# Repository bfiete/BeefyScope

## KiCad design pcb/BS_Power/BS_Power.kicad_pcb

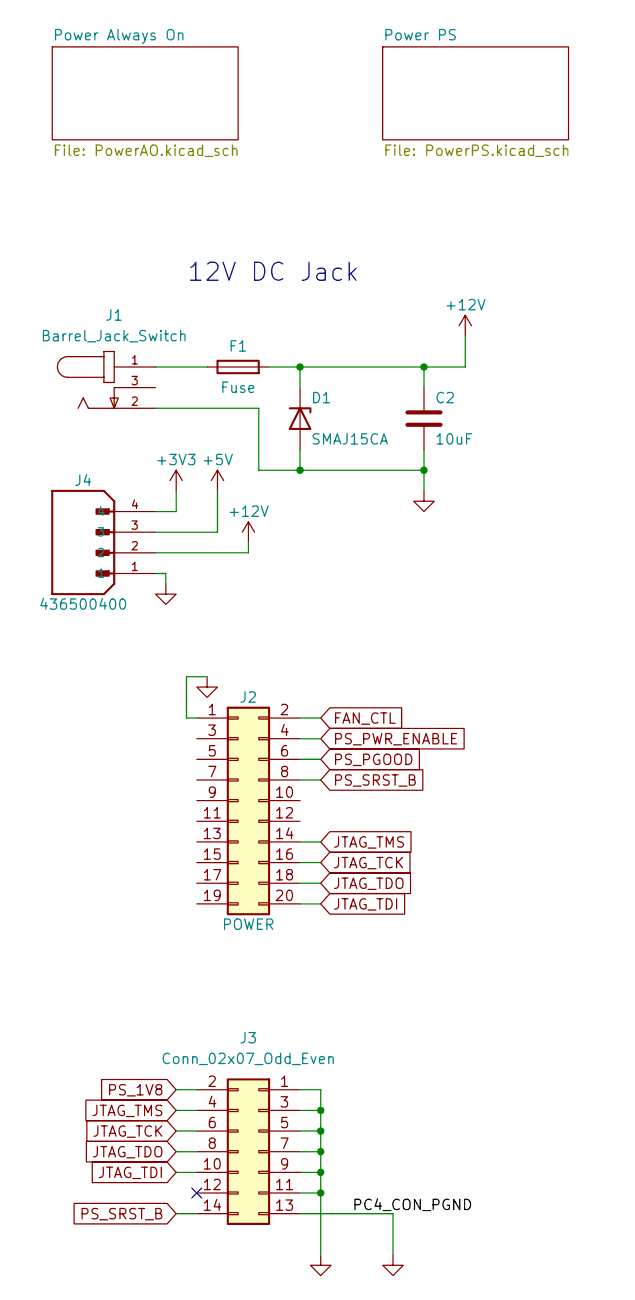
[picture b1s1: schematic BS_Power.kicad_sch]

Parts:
C2: 10uF; C_0805_2012Metric
D1: SMAJ15CA; D_SMA; LCSC Part C353477
F1: Fuse; FUSE_C206912; LCSC Part C206912
J1: Barrel_Jack_Switch; CUI_PJ-202BH; PART_REV 1.02; JLCPCB BOM 0
J2: POWER; IDC-Header_2x10_P2.54mm_Vertical; LCSC Part C9144
J3: Conn_02x07_Odd_Even; PinHeader_2x07_P2.00mm_Vertical; LCSC Part C146614
J4: 436500400; MOLEX_436500400; PARTREV D7; LCSC Part C277684

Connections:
+3V3: J4.4; also elsewhere on the board
+5V: J4.3; also elsewhere on the board
+12V: C2.1, D1.1 (K), F1.2, J4.2; also elsewhere on the board
FAN_CTL: J2.2
GND: C2.2, D1.2 (A), J1.2, J2.1, J3.1, J3.3, J3.5, J3.7, J3.9, J3.11, J3.13, J4.1; also elsewhere on the board
JTAG_TCK: J2.16, J3.6
JTAG_TDI: J2.20, J3.10
JTAG_TDO: J2.18, J3.8
JTAG_TMS: J2.14, J3.4
unnamed: F1.1, J1.1
PS_1V8: J3.2
PS_PGOOD: J2.6; also elsewhere on the board
PS_PWR_ENABLE: J2.4; also elsewhere on the board
PS_SRST_B: J2.8, J3.14

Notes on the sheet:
12V DC Jack

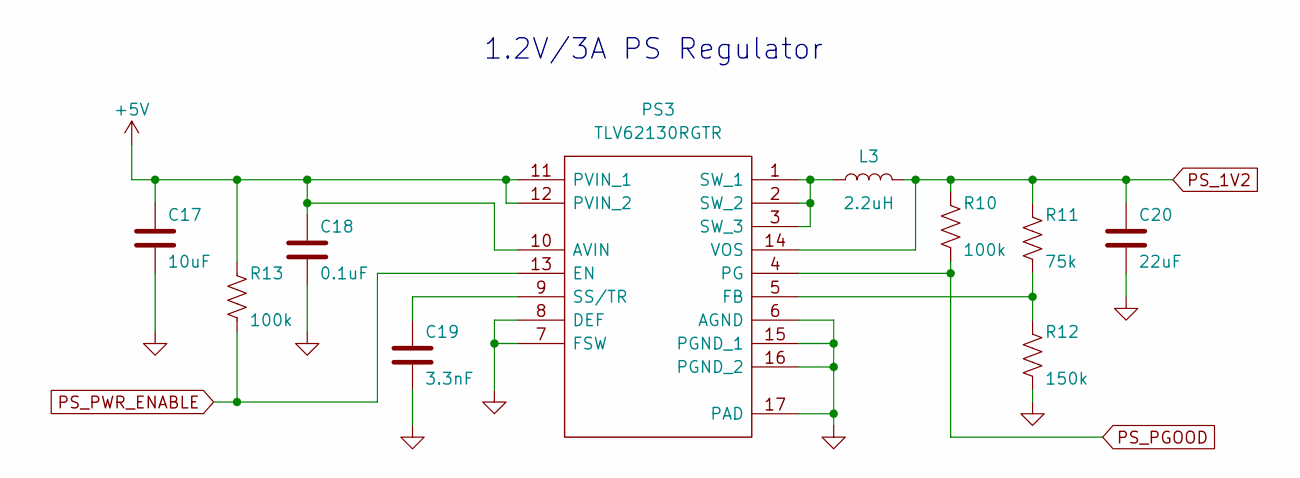
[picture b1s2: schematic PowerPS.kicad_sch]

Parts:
C17: 10uF; C_0805_2012Metric
C18: 0.1uF; C_0603_1608Metric
C19: 3.3nF; C_0603_1608Metric
C20: 22uF; C_0805_2012Metric
L3: 2.2uH; L_4.1x4.5; LCSC Part C2847469
PS3: TLV62130RGTR; QFN50P300X300X100-17N-D; Mouser Part Number 595-TLV62130RGTR
R10, R13: 100k; R_0603_1608Metric
R11: 75k; R_0603_1608Metric; LCSC Part C23240
R12: 150k; R_0603_1608Metric; LCSC Part C22807

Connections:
+5V: C17.1, C18.1, PS3.10 (AVIN), PS3.11 (PVIN_1), PS3.12 (PVIN_2), R13.1; also elsewhere on the board
GND: C17.2, C18.2, C19.1, C20.2, PS3.6 (AGND), PS3.7 (FSW), PS3.8 (DEF), PS3.15 (PGND_1), PS3.16 (PGND_2), PS3.17 (PAD), R12.2; also elsewhere on the board
unnamed: C19.2, PS3.9 (SS/TR)
unnamed: L3.1, PS3.1 (SW_1), PS3.2 (SW_2), PS3.3 (SW_3)
unnamed: PS3.5 (FB), R11.2, R12.1
PS_1V2: C20.1, L3.2, PS3.14 (VOS), R10.1, R11.1
PS_PGOOD: PS3.4 (PG), R10.2; also elsewhere on the board
PS_PWR_ENABLE: PS3.13 (EN), R13.2; also elsewhere on the board

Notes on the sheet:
1.2V/3A PS Regulator

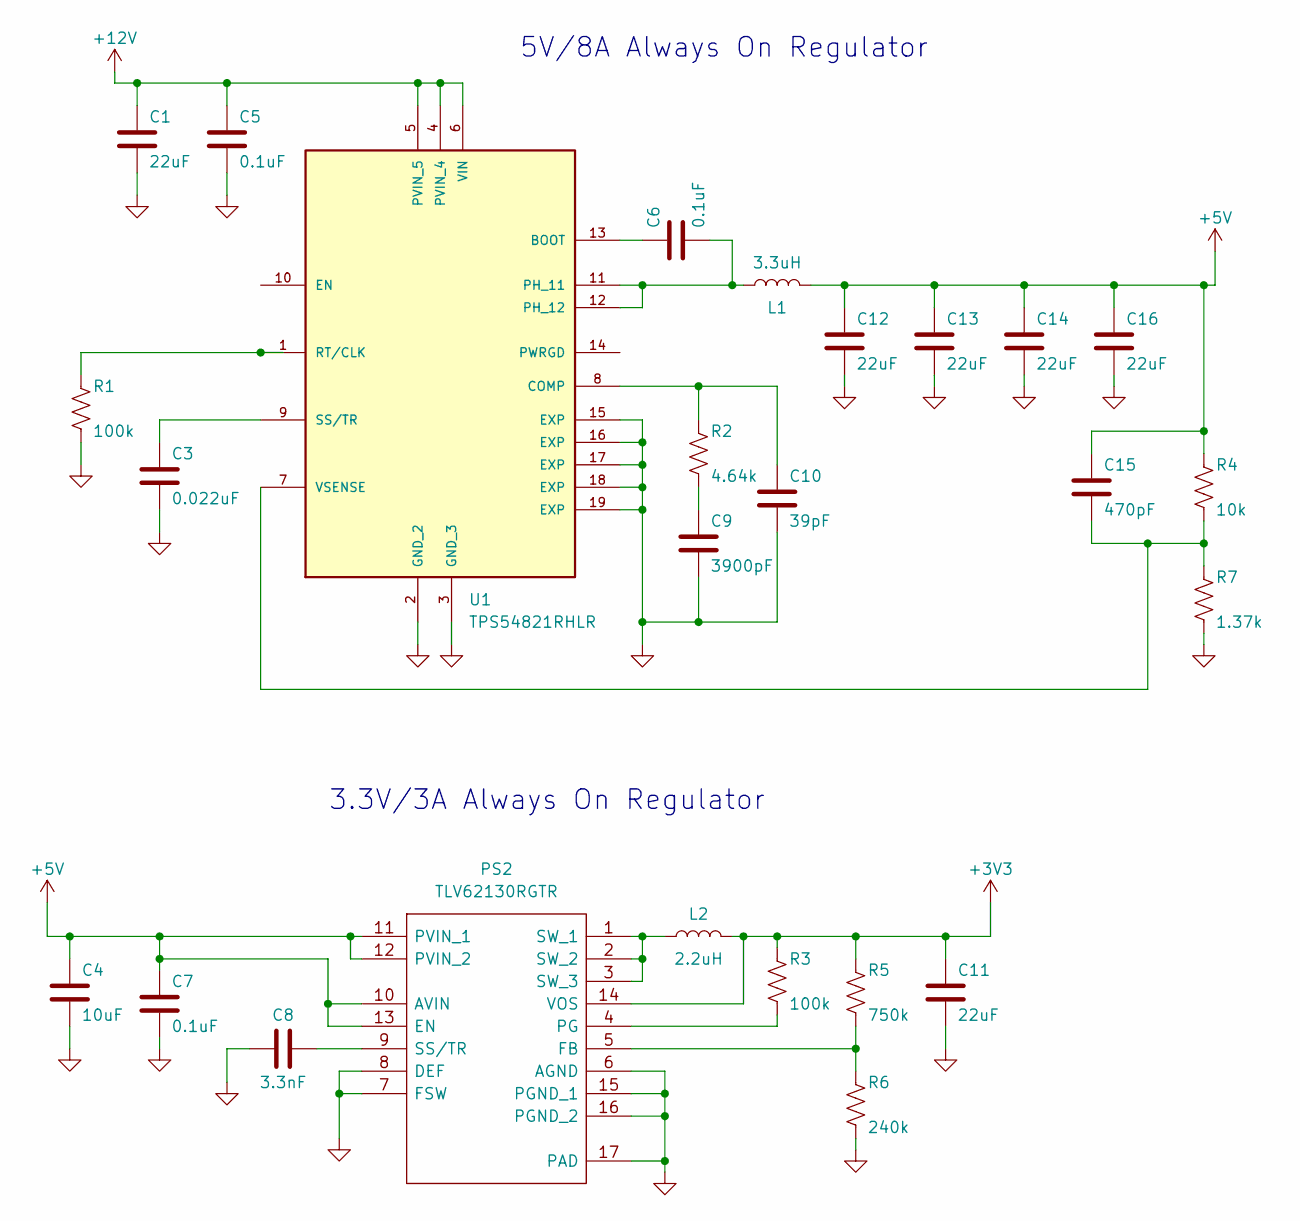
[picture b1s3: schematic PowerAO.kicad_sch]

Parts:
C1, C11, C12, C13, C14, C16: 22uF; C_0805_2012Metric
C3: 0.022uF; C_0603_1608Metric
C4: 10uF; C_0805_2012Metric
C5, C6, C7: 0.1uF; C_0603_1608Metric
C8: 3.3nF; C_0603_1608Metric
C9: 3900pF; C_0603_1608Metric
C10: 39pF; C_0603_1608Metric
C15: 470pF; C_0603_1608Metric
L1: 3.3uH; L_6.7x7; LCSC Part C2761959
L2: 2.2uH; L_4.1x4.5; LCSC Part C2847469
PS2: TLV62130RGTR; QFN50P300X300X100-17N-D; Mouser Part Number 595-TLV62130RGTR
R1, R3: 100k; R_0603_1608Metric
R2: 4.64k; R_0402_1005Metric; LCSC Part C60154
R4: 10k; R_0402_1005Metric; LCSC Part C852428
R5: 750k; R_0603_1608Metric
R6: 240k; R_0603_1608Metric
R7: 1.37k; R_0402_1005Metric; LCSC Part C705664
U1: TPS54821RHLR; IC_TPS54821RHLR; PARTREV 4205346-2/K 01/17

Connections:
+3V3: C11.1, L2.2, PS2.14 (VOS), R3.1, R5.1; also elsewhere on the board
+5V: C4.1, C7.1, C12.1, C13.1, C14.1, C15.1, C16.1, L1.2, PS2.10 (AVIN), PS2.11 (PVIN_1), PS2.12 (PVIN_2), PS2.13 (EN), R4.1; also elsewhere on the board
+12V: C1.1, C5.1, U1.4 (PVIN_4), U1.5 (PVIN_5), U1.6 (VIN); also elsewhere on the board
GND: C1.2, C3.2, C4.2, C5.2, C7.2, C8.1, C9.2, C10.2, C11.2, C12.2, C13.2, C14.2, C16.2, PS2.6 (AGND), PS2.7 (FSW), PS2.8 (DEF), PS2.15 (PGND_1), PS2.16 (PGND_2), PS2.17 (PAD), R1.2, R6.2, R7.2, U1.2 (GND_2), U1.3 (GND_3), U1.15 (EXP), U1.16 (EXP), U1.17 (EXP), U1.18 (EXP), U1.19 (EXP); also elsewhere on the board
unnamed: C3.1, U1.9 (SS/TR)
unnamed: C6.1, U1.13 (BOOT)
unnamed: C6.2, L1.1, U1.11 (PH_11), U1.12 (PH_12)
unnamed: C8.2, PS2.9 (SS/TR)
unnamed: C9.1, R2.2
unnamed: C10.1, R2.1, U1.8 (COMP)
unnamed: C15.2, R4.2, R7.1, U1.7 (VSENSE)
unnamed: L2.1, PS2.1 (SW_1), PS2.2 (SW_2), PS2.3 (SW_3)
unnamed: PS2.4 (PG), R3.2
unnamed: PS2.5 (FB), R5.2, R6.1
unnamed: R1.1, U1.1 (RT/CLK)

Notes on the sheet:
3.3V/3A Always On Regulator
5V/8A Always On Regulator

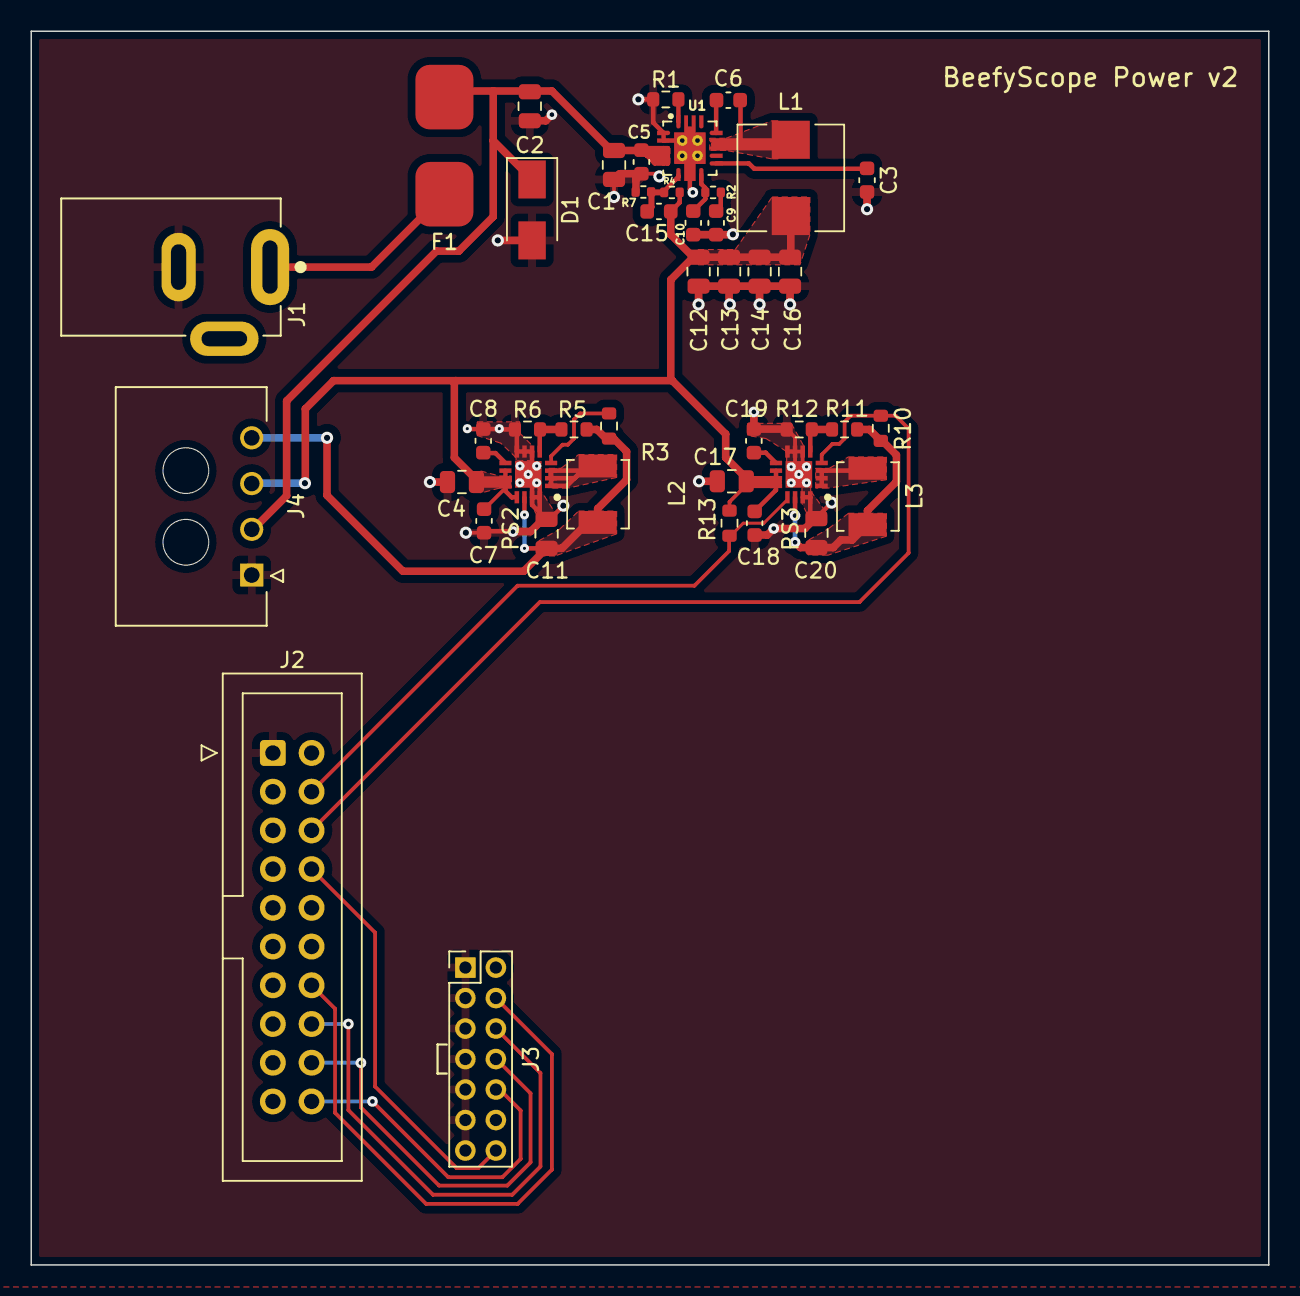
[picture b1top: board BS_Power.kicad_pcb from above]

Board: 2 copper layers, 81.2 x 80.9 mm, 43 parts (0 on the bottom side), 27 nets.

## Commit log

2022-11-11 Initial source
2022-11-11 Build files
2022-11-11 LOD fixes
2022-11-17 BS_Power
2022-11-18 Before 5V regulator replacement
2022-11-22 BS_Power updates
2022-12-12 BSPower V2
